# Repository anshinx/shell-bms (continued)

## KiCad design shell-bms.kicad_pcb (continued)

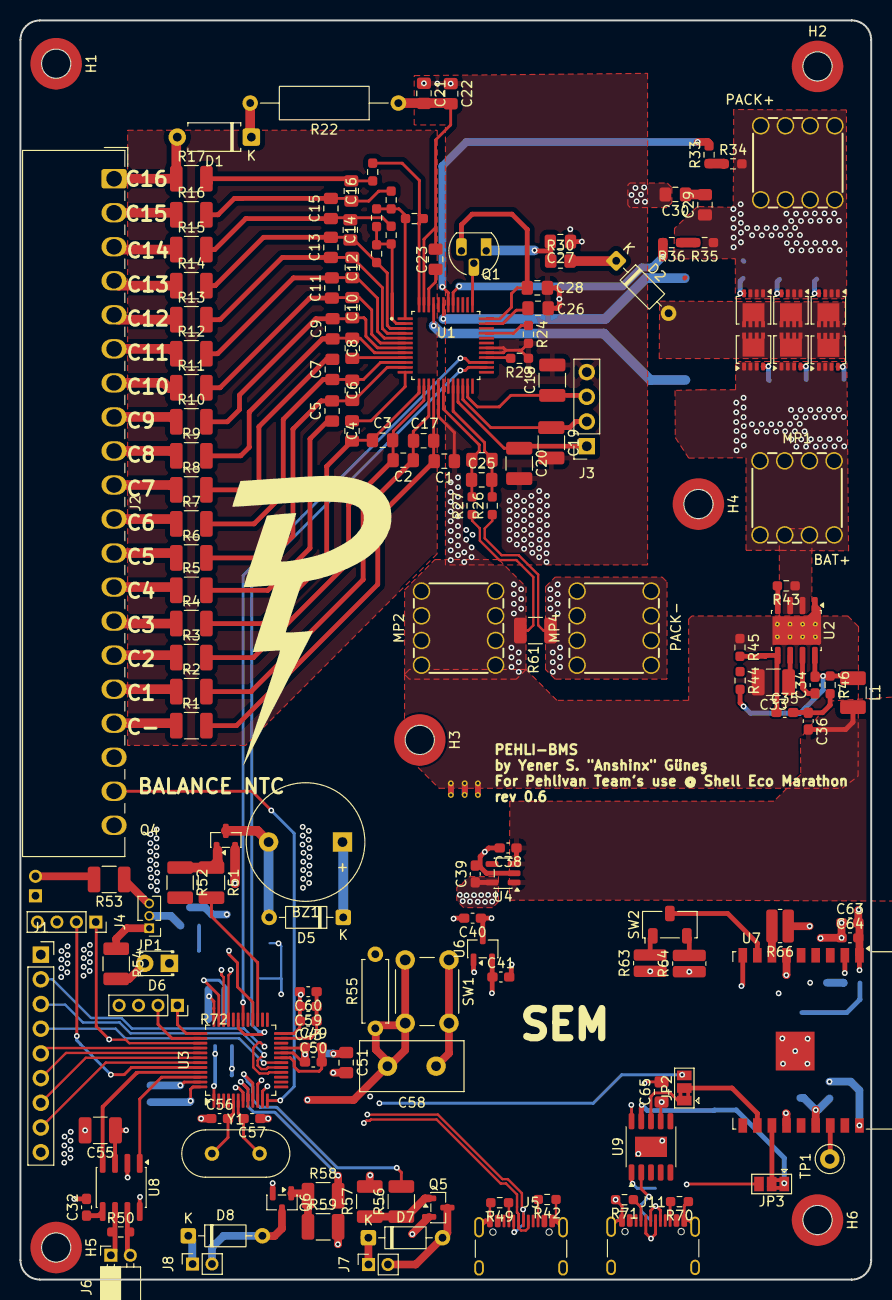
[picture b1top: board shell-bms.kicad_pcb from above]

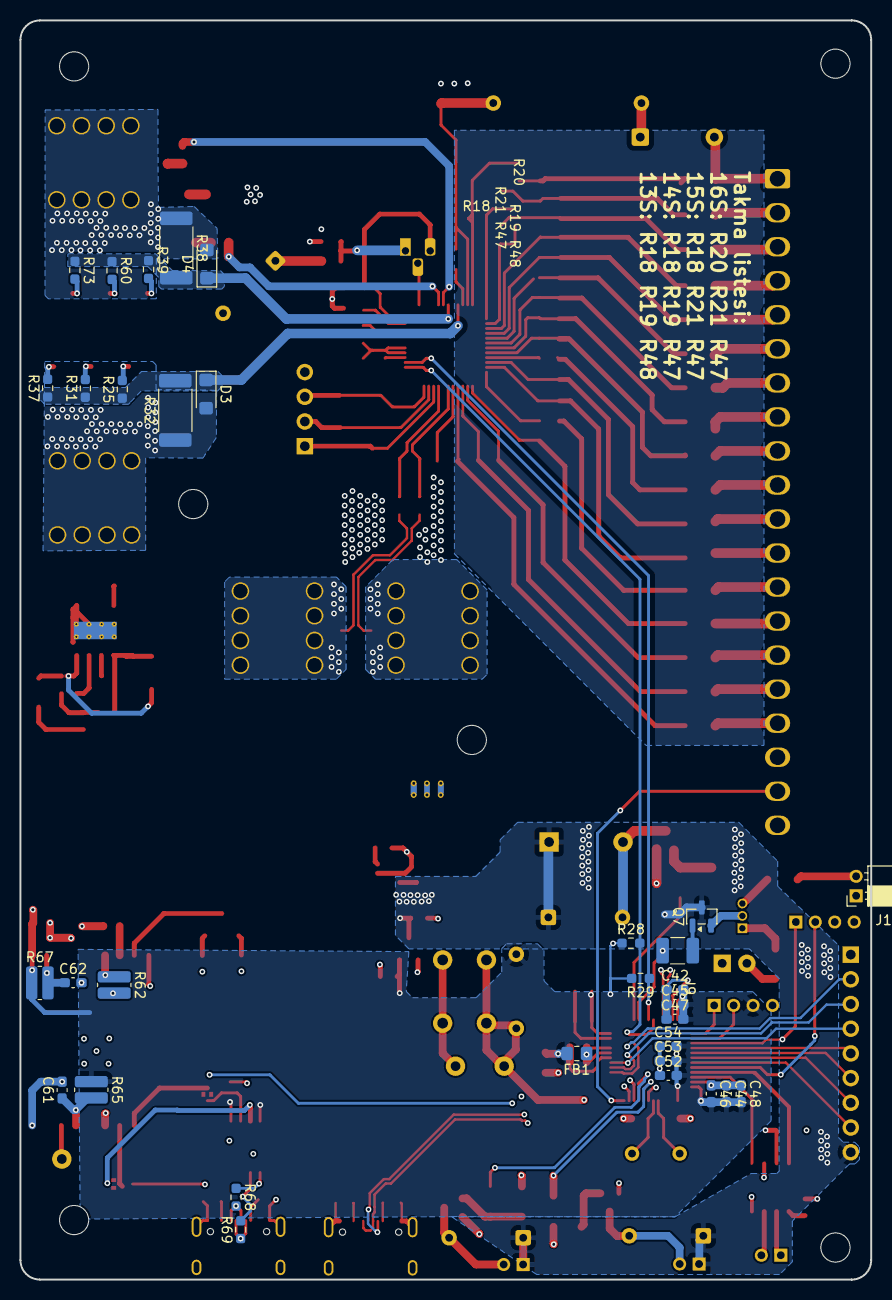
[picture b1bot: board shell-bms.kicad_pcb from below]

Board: 4 copper layers, 87.5 x 129.5 mm, 195 parts (32 on the bottom side), 142 nets.

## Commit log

2026-01-02 lots of lots changes. Schematic done NEEDS Review
2026-01-28 son update
2026-02-12 finalised product
2026-02-13 near end
2026-02-13 bit artık
2026-02-20 esp-32 layout changes
2026-02-26 BMS DONE IHOPE
